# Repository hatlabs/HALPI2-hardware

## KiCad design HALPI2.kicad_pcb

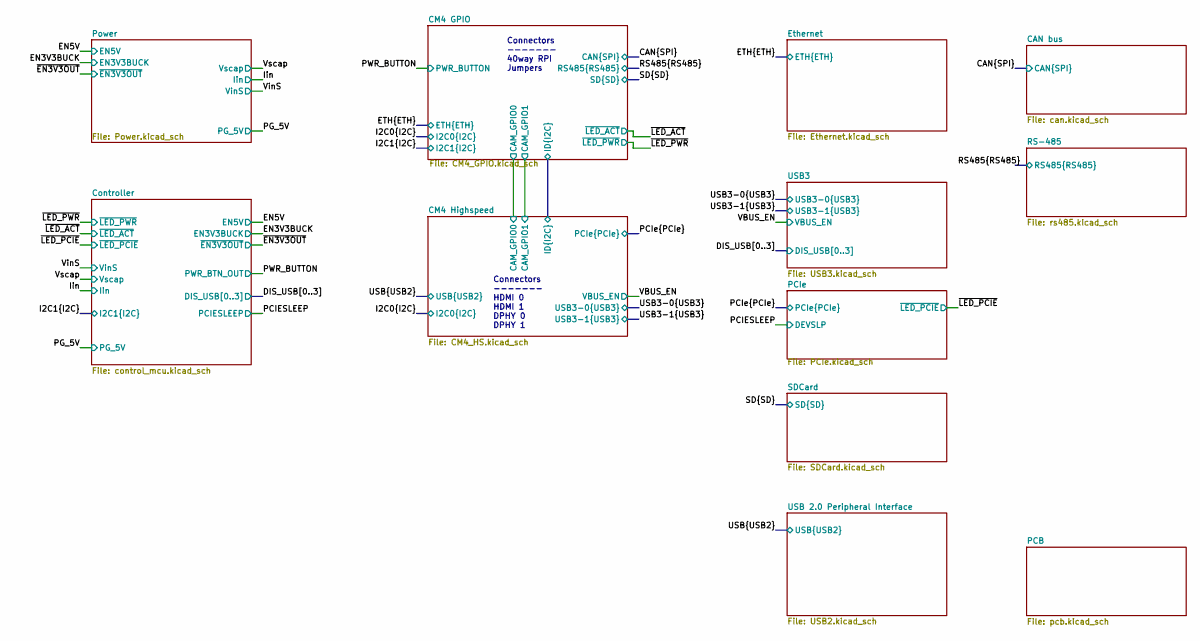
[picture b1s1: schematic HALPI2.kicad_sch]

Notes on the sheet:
Connectors ------- HDMI 0 HDMI 1 DPHY 0 DPHY 1
Connectors ------- 40way RPI Jumpers

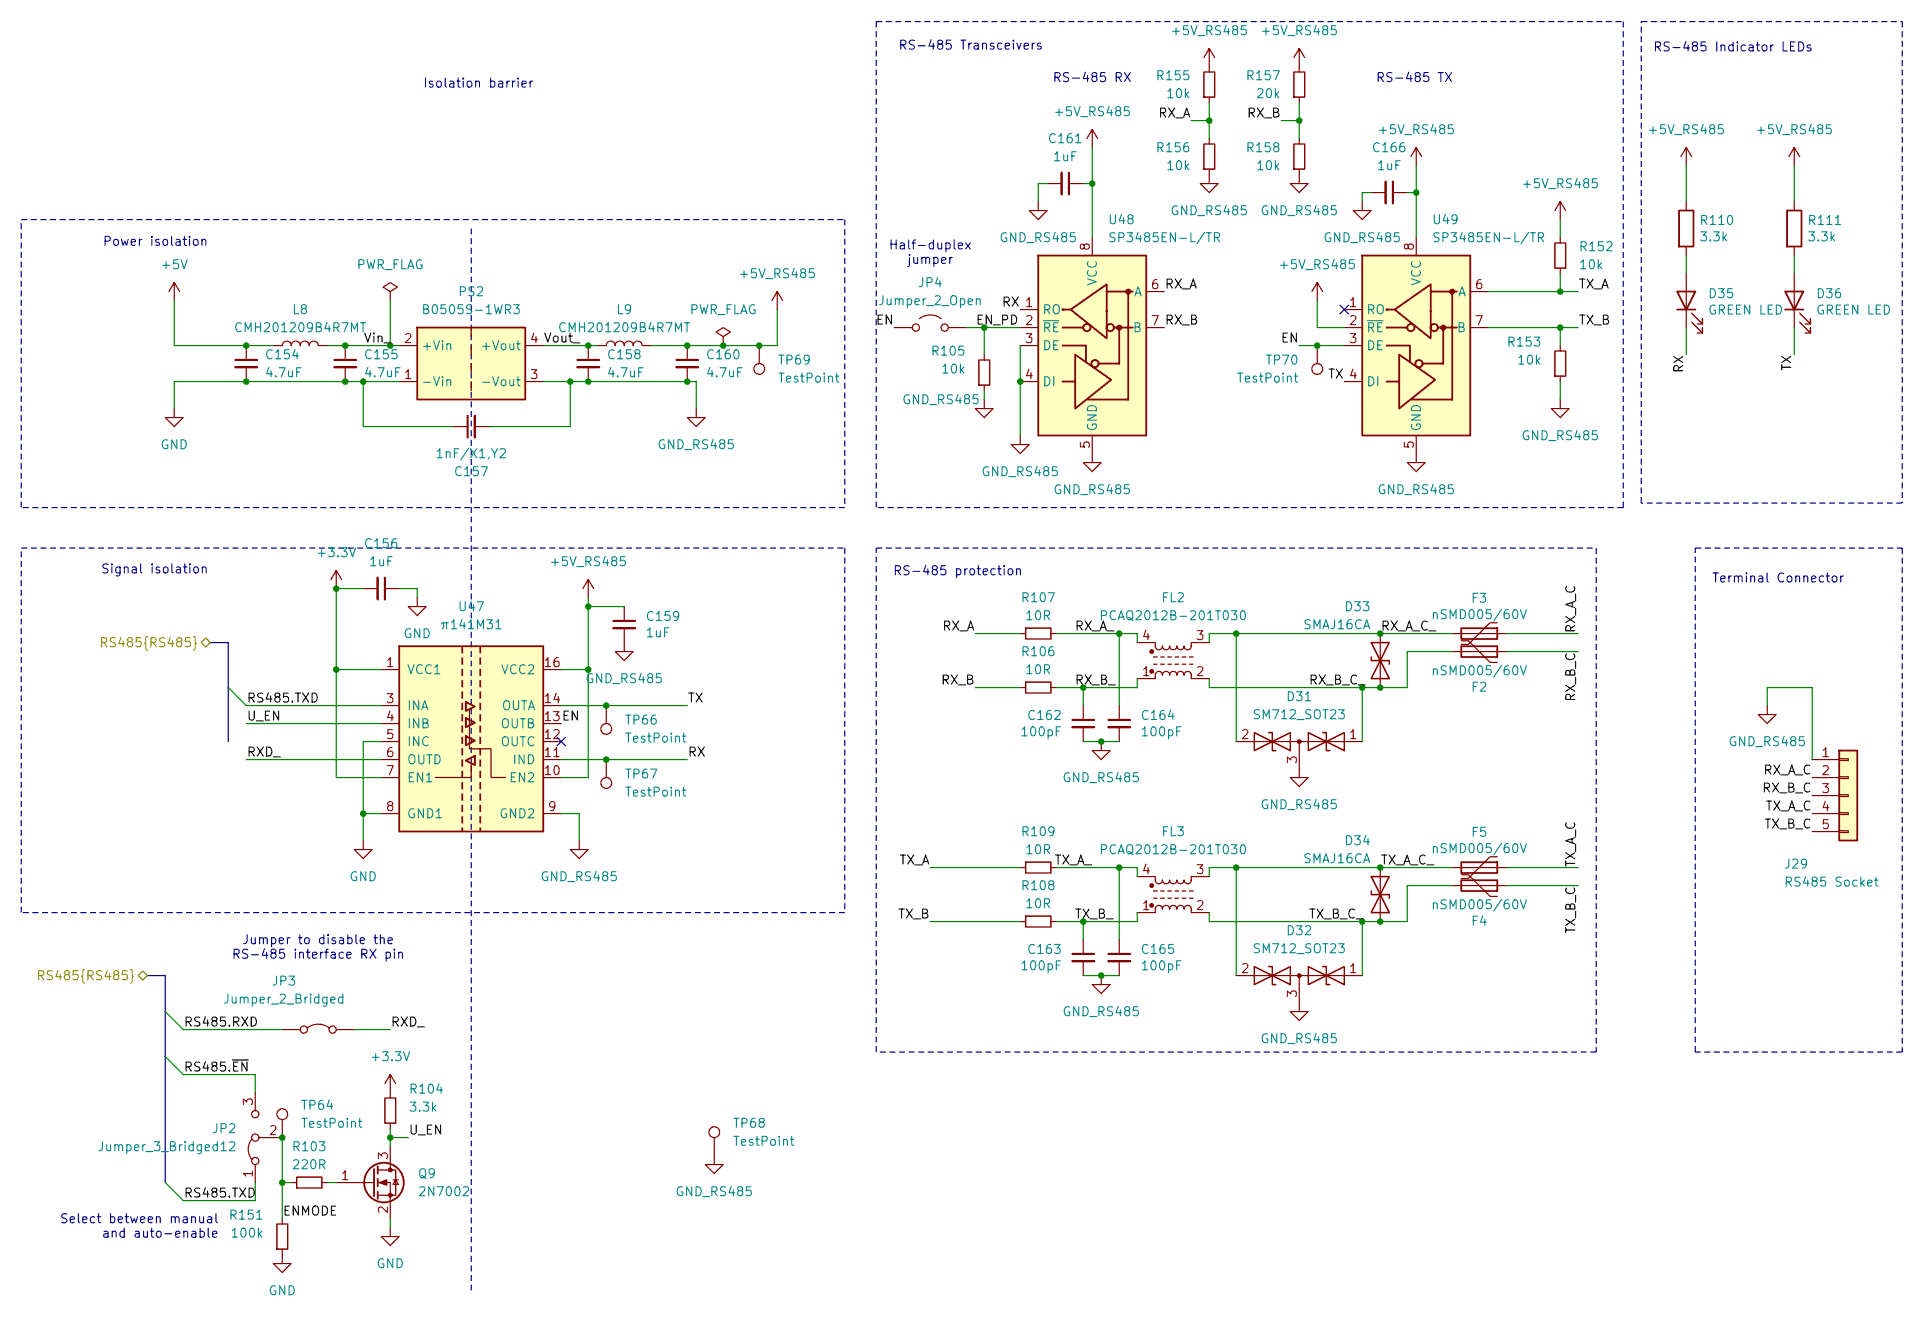
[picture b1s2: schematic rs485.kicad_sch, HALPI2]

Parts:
C154, C155, C158, C160: 4.7uF; C_0603_1608Metric; LCSC C19666
C156, C159, C161, C166: 1uF; C_0402_1005Metric; LCSC C52923
C157: 1nF/X1,Y2; C_1808_4520Metric; LCSC C784081
C162, C163, C164, C165: 100pF; C_0603_1608Metric; LCSC C14858
D31, D32: SM712_SOT23; SOT-23; LCSC C7420375
D33, D34: SMAJ16CA; D_SMA; LCSC C19077537
D35, D36: GREEN LED; LED_0603_1608Metric; LCSC C965804
F2, F3, F4, F5: nSMD005/60V; Fuse_1206_3216Metric; LCSC C2830235
FL2, FL3: PCAQ2012B-201T030; L_CommonModeChoke_PCAQ2012B; LCSC C2926967
J29: RS485 Socket; PhoenixContact_MCV_1,5_5-G-3.81_1x05_P3.81mm_Vertical; LCSC C8391
JP2: Jumper_3_Bridged12; PinHeader_1x03_P2.54mm_Vertical_SMD_Pin1Left; LCSC C41417360
JP3: Jumper_2_Bridged; PinHeader_1x02_P2.54mm_Vertical; LCSC C492401
JP4: Jumper_2_Open; PinHeader_1x02_P2.54mm_Vertical; LCSC C492401
L8, L9: CMH201209B4R7MT; L_0805_2012Metric; LCSC C394959
PS2: B0505S-1WR3; SIP-4_L11.7-W6.0-P2.54_B0305S-1WR3; LCSC C7465178
Q9: 2N7002; SOT-23; LCSC C8545
R103: 220R; R_0402_1005Metric; LCSC C25091
R104, R110, R111: 3.3k; R_0402_1005Metric; LCSC C25890
R105, R152, R153, R155, R156, R158: 10k; R_0402_1005Metric; LCSC C25744
R106, R107, R108, R109: 10R; R_0402_1005Metric; LCSC C25077
R151: 100k; R_0402_1005Metric; LCSC C25741
R157: 20k; R_0402_1005Metric; LCSC C25765
TP64, TP66, TP67, TP69, TP70: TestPoint; TestPoint_Pad_D1.0mm
TP68: TestPoint; TestPoint_Pad_1.5x1.5mm
U47: π141M31; SOIC-16_3.9x9.9mm_P1.27mm; LCSC C471605
U48, U49: SP3485EN-L/TR; SOIC-8_3.9x4.9mm_P1.27mm; LCSC C8963

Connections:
+3.3V: C156.2, R104.2, U47.1 (VCC1), U47.7 (EN1); also elsewhere on the board
+5V: C154.1, L8.1; also elsewhere on the board
+5V_RS485: C159.1, C160.1, C161.1, C166.1, L9.2, R110.1, R111.1, R152.2, R155.2, R157.2, TP69.1 (1_1), U47.10 (EN2), U47.16 (VCC2), U48.8 (VCC), U49.2 (~RE), U49.8 (VCC)
/RS485.RXD: JP3.1 (A); also elsewhere on the board
/RS485.TXD: JP2.1 (A), U47.3 (INA); also elsewhere on the board
/RS485.~EN: JP2.3 (B); also elsewhere on the board
/RS-485/EN: JP4.1 (A), TP70.1 (1_1), U47.13 (OUTB), U49.3 (DE)
/RS-485/ENMODE: JP2.2 (C), R103.1, R151.2, TP64.1 (1_1)
/RS-485/EN_PD: JP4.2 (B), R105.2, U48.2 (~RE)
/RS-485/RX: D35.1 (K), TP67.1 (1_1), U47.11 (IND), U48.1 (RO)
/RS-485/RXD_: JP3.2 (B), U47.6 (OUTD)
/RS-485/RX_A: R107.1, R155.1, R156.2, U48.6 (A)
/RS-485/RX_A_: C164.1, FL2.4, R107.2
/RS-485/RX_A_C: F3.1, J29.2
/RS-485/RX_A_C_: D31.2 (A2), D33.1 (A1), F3.2, FL2.3
/RS-485/RX_B: R106.1, R157.1, R158.2, U48.7 (B)
/RS-485/RX_B_: C162.1, FL2.1, R106.2
/RS-485/RX_B_C: F2.1, J29.3
/RS-485/RX_B_C_: D31.1 (A1), D33.2 (A2), F2.2, FL2.2
/RS-485/TX: D36.1 (K), TP66.1 (1_1), U47.14 (OUTA), U49.4 (DI)
/RS-485/TX_A: R109.1, R152.1, U49.6 (A)
/RS-485/TX_A_: C165.1, FL3.4, R109.2
/RS-485/TX_A_C: F5.1, J29.4
/RS-485/TX_A_C_: D32.2 (A2), D34.1 (A1), F5.2, FL3.3
/RS-485/TX_B: R108.1, R153.2, U49.7 (B)
/RS-485/TX_B_: C163.1, FL3.1, R108.2
/RS-485/TX_B_C: F4.1, J29.5
/RS-485/TX_B_C_: D32.1 (A1), D34.2 (A2), F4.2, FL3.2
/RS-485/U_EN: Q9.3 (D), R104.1, U47.4 (INB)
/RS-485/Vin_: C155.1, L8.2, PS2.2 (+Vin)
/RS-485/Vout_: C158.1, L9.1, PS2.4 (+Vout)
GND: C154.2, C155.2, C156.1, C157.1, PS2.1 (-Vin), Q9.2 (S), R151.1, U47.2 (GND1), U47.5 (INC), U47.8 (GND1); also elsewhere on the board
GND_RS485: C157.2, C158.2, C159.2, C160.2, C161.2, C162.2, C163.2, C164.2, C165.2, C166.2, D31.3 (common), D32.3 (common), J29.1, PS2.3 (-Vout), R105.1, R153.1, R156.1, R158.1, TP68.1 (1_1), U47.9 (GND2), U47.15 (GND2), U48.3 (DE), U48.4 (DI), U48.5 (GND), U49.5 (GND)
unnamed: D35.2 (A), R110.2
unnamed: D36.2 (A), R111.2
unnamed: Q9.1 (G), R103.2

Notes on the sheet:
RS-485 TX
Power isolation
RS-485 RX
Signal isolation
Terminal Connector
Jumper to disable the RS-485 interface RX pin
Isolation barrier
Half-duplex jumper
RS-485 Indicator LEDs
RS-485 Transceivers
Select between manual and auto-enable
RS-485 protection

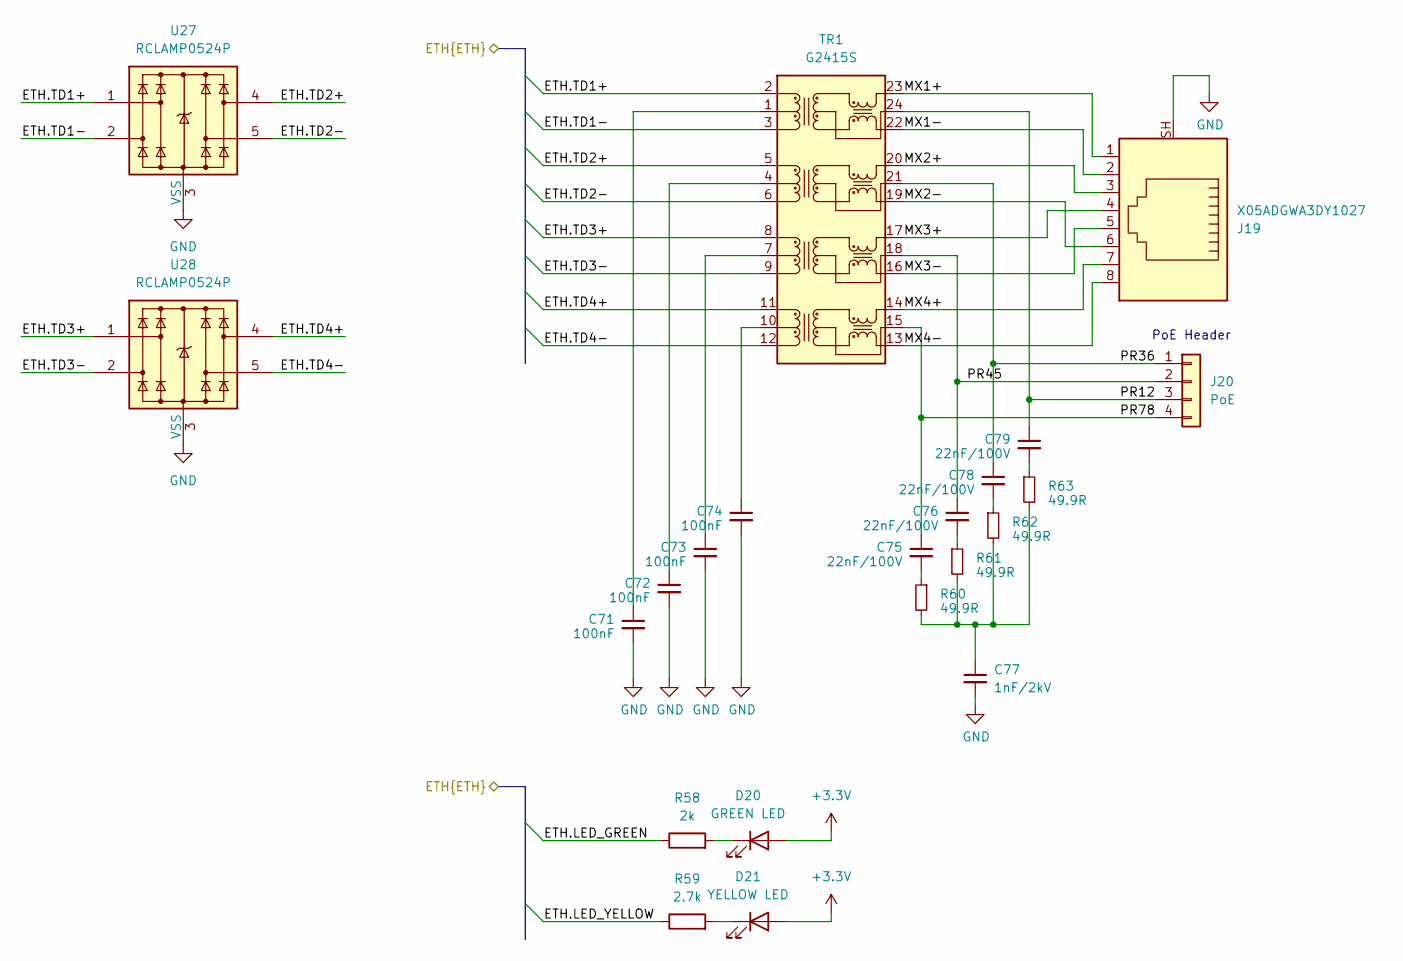
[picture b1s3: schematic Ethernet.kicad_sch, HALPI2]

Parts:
C71, C72, C73, C74: 100nF; C_0402_1005Metric; LCSC C1525
C75, C76, C78, C79: 22nF/100V; C_0603_1608Metric; LCSC C313083
C77: 1nF/2kV; C_1206_3216Metric; LCSC C9196
D20: GREEN LED; LED_0603_1608Metric; LCSC C965804
D21: YELLOW LED; LED_0603_1608Metric; LCSC C89811
J19: X05ADGWA3DY1027; RJ45-TH_XKB_X05ADGWA3DY1027; LCSC C2916454
J20: PoE; PinSocket_2x02_P2.54mm_Vertical_SMD; LCSC C5160817
R58: 2k; R_0603_1608Metric; LCSC C22975
R59: 2.7k; R_0603_1608Metric; LCSC C13167
R60, R61, R62, R63: 49.9R; R_0402_1005Metric; LCSC C25120
TR1: G2415S; Transformer_Ethernet_YDS_30F-51NL_SO-24_7.1x15.1mm; LCSC C3003219
U27, U28: RCLAMP0524P; Diodes_UDFN-10_1.0x2.5mm_P0.5mm; LCSC C907837

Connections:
+3.3V: D20.2 (A), D21.2 (A); also elsewhere on the board
/ETH.LED_GREEN: R58.1; also elsewhere on the board
/ETH.LED_YELLOW: R59.1; also elsewhere on the board
/ETH.TD1+: TR1.2 (TD1+), U27.1, U27.10; also elsewhere on the board
/ETH.TD1-: TR1.3 (TD1-), U27.2, U27.9; also elsewhere on the board
/ETH.TD2+: TR1.5 (TD2+), U27.4, U27.7; also elsewhere on the board
/ETH.TD2-: TR1.6 (TD2-), U27.5, U27.6; also elsewhere on the board
/ETH.TD3+: TR1.8 (TD3+), U28.1, U28.10; also elsewhere on the board
/ETH.TD3-: TR1.9 (TD3-), U28.2, U28.9; also elsewhere on the board
/ETH.TD4+: TR1.11 (TD4+), U28.4, U28.7; also elsewhere on the board
/ETH.TD4-: TR1.12 (TD4-), U28.5, U28.6; also elsewhere on the board
/Ethernet/MX1+: J19.1, TR1.23 (MX1+)
/Ethernet/MX1-: J19.2, TR1.22 (MX1-)
/Ethernet/MX2+: J19.3, TR1.20 (MX2+)
/Ethernet/MX2-: J19.6, TR1.19 (MX2-)
/Ethernet/MX3+: J19.4, TR1.17 (MX3+)
/Ethernet/MX3-: J19.5, TR1.16 (MX3-)
/Ethernet/MX4+: J19.7, TR1.14 (MX4+)
/Ethernet/MX4-: J19.8, TR1.13 (MX4-)
/Ethernet/PR12: C79.1, J20.3, TR1.24 (CT)
/Ethernet/PR36: C78.1, J20.1, TR1.21 (CT)
/Ethernet/PR45: C76.1, J20.2, TR1.18 (CT)
/Ethernet/PR78: C75.1, J20.4, TR1.15 (CT)
GND: C71.2, C72.2, C73.2, C74.2, C77.2, J19.SH, U27.3 (VSS), U27.8 (VSS), U28.3 (VSS), U28.8 (VSS); also elsewhere on the board
unnamed: C71.1, TR1.1 (CT)
unnamed: C72.1, TR1.4 (CT)
unnamed: C73.1, TR1.7 (CT)
unnamed: C74.1, TR1.10 (CT)
unnamed: C75.2, R60.1
unnamed: C76.2, R61.1
unnamed: C77.1, R60.2, R61.2, R62.2, R63.2
unnamed: C78.2, R62.1
unnamed: C79.2, R63.1
unnamed: D20.1 (K), R58.2
unnamed: D21.1 (K), R59.2

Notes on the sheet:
PoE Header

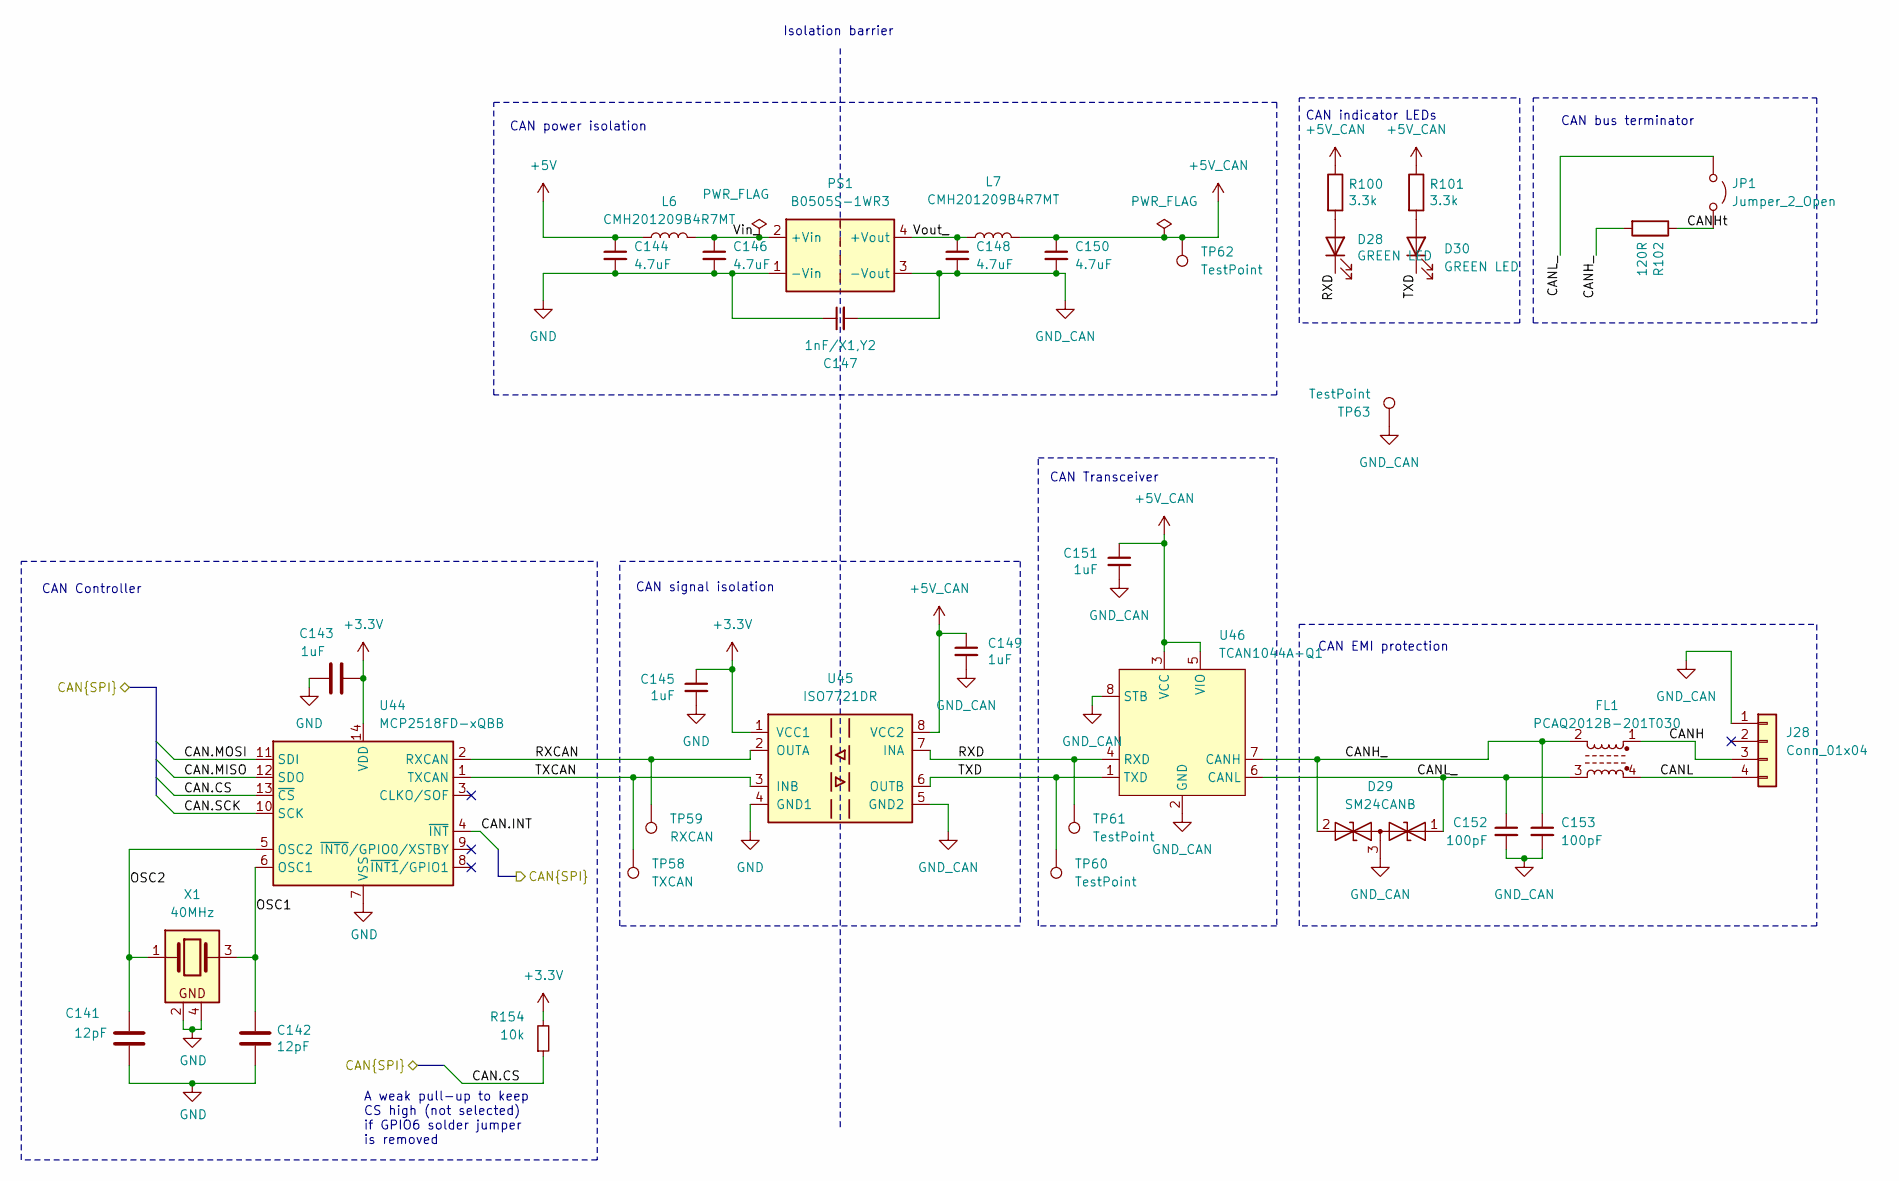
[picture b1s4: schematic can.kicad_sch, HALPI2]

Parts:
C141, C142: 12pF; C_0402_1005Metric; LCSC C1547
C143, C145, C149, C151: 1uF; C_0402_1005Metric; LCSC C52923
C144, C146, C148, C150: 4.7uF; C_0603_1608Metric; LCSC C19666
C147: 1nF/X1,Y2; C_1808_4520Metric; LCSC C784081
C152, C153: 100pF; C_0603_1608Metric; LCSC C14858
D28, D30: GREEN LED; LED_0603_1608Metric; LCSC C965804
D29: SM24CANB; SOT-23; LCSC C19185908
FL1: PCAQ2012B-201T030; L_CommonModeChoke_PCAQ2012B; LCSC C2926967
J28: Conn_01x04; PhoenixContact_MCV_1,5_4-G-3.81_1x04_P3.81mm_Vertical; LCSC C8410
JP1: Jumper_2_Open; PinHeader_1x02_P2.54mm_Vertical; LCSC C492401
L6, L7: CMH201209B4R7MT; L_0805_2012Metric; LCSC C394959
PS1: B0505S-1WR3; SIP-4_L11.7-W6.0-P2.54_B0305S-1WR3; LCSC C7465178
R100, R101: 3.3k; R_0402_1005Metric; LCSC C25890
R102: 120R; R_0805_2012Metric; LCSC C17437
R154: 10k; R_0402_1005Metric; LCSC C25744
TP58: TXCAN; TestPoint_Pad_D1.0mm
TP59: RXCAN; TestPoint_Pad_D1.0mm
TP60, TP61, TP62: TestPoint; TestPoint_Pad_D1.0mm
TP63: TestPoint; TestPoint_Pad_1.5x1.5mm
U44: MCP2518FD-xQBB; DFN-14-1EP_3x4.5mm_P0.65mm_EP1.65x4.25mm; LCSC C621395
U45: ISO7721DR; SOIC-8_3.9x4.9mm_P1.27mm; LCSC C366164
U46: TCAN1044A-Q1; SOIC-8_3.9x4.9mm_P1.27mm; LCSC C3235016
X1: 40MHz; Crystal_SMD_3225-4Pin_3.2x2.5mm; LCSC C5380554

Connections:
+3.3V: C143.2, C145.1, R154.2, U44.14 (VDD), U45.1 (VCC1); also elsewhere on the board
+5V: C144.1, L6.1; also elsewhere on the board
+5V_CAN: C149.1, C150.1, C151.1, L7.2, R100.1, R101.1, TP62.1 (1_1), U45.8 (VCC2), U46.3 (VCC), U46.5 (VIO)
/CAN bus/CANH: FL1.1, J28.3
/CAN bus/CANH_: C153.1, D29.2 (A2), FL1.2, R102.2, U46.7 (CANH)
/CAN bus/CANHt: JP1.2 (B), R102.1
/CAN bus/CANL: FL1.4, J28.4
/CAN bus/CANL_: C152.1, D29.1 (A1), FL1.3, JP1.1 (A), U46.6 (CANL)
/CAN bus/OSC1: C142.1, U44.6 (OSC1), X1.3
/CAN bus/OSC2: C141.1, U44.5 (OSC2), X1.1
/CAN bus/RXCAN: TP59.1 (1_1), U44.2 (RXCAN), U45.2 (OUTA)
/CAN bus/RXD: D28.1 (K), TP61.1 (1_1), U45.7 (INA), U46.4 (RXD)
/CAN bus/TXCAN: TP58.1 (1_1), U44.1 (TXCAN), U45.3 (INB)
/CAN bus/TXD: D30.1 (K), TP60.1 (1_1), U45.6 (OUTB), U46.1 (TXD)
/CAN bus/Vin_: C146.1, L6.2, PS1.2 (+Vin)
/CAN bus/Vout_: C148.1, L7.1, PS1.4 (+Vout)
/CAN.CS: R154.1, U44.13 (~CS); also elsewhere on the board
/CAN.INT: U44.4 (~INT); also elsewhere on the board
/CAN.MISO: U44.12 (SDO); also elsewhere on the board
/CAN.MOSI: U44.11 (SDI); also elsewhere on the board
/CAN.SCK: U44.10 (SCK); also elsewhere on the board
GND: C141.2, C142.2, C143.1, C144.2, C145.2, C146.2, C147.1, PS1.1 (-Vin), U44.7 (VSS), U44.15 (VSS), U45.4 (GND1), X1.2, X1.4; also elsewhere on the board
GND_CAN: C147.2, C148.2, C149.2, C150.2, C151.2, C152.2, C153.2, D29.3 (common), J28.1, PS1.3 (-Vout), TP63.1 (1_1), U45.5 (GND2), U46.2 (GND), U46.8 (STB)
unnamed: D28.2 (A), R100.2
unnamed: D30.2 (A), R101.2

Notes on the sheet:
CAN signal isolation
CAN Transceiver
CAN Controller
Isolation barrier
CAN power isolation
CAN bus terminator
CAN EMI protection
CAN indicator LEDs
A weak pull-up to keep CS high (not selected) if GPIO6 solder jumper is removed

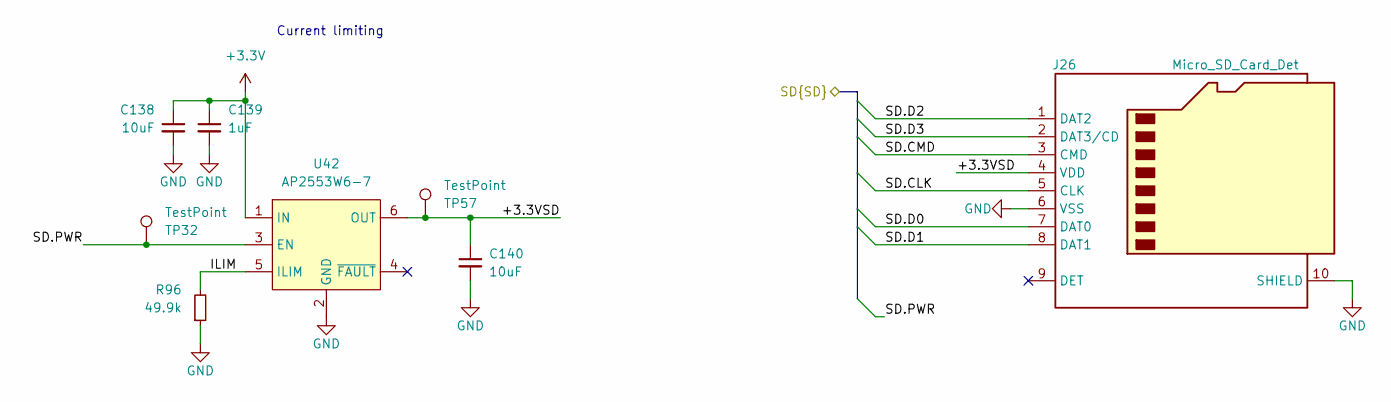
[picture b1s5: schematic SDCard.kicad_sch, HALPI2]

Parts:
C138, C140: 10uF; C_0805_2012Metric; LCSC C15850
C139: 1uF; C_0402_1005Metric; LCSC C52923
J26: Micro_SD_Card_Det; MicroSD_SHOU-HAN_TF-PUSH; LCSC C393941
R96: 49.9k; R_0603_1608Metric; LCSC C23184
TP32, TP57: TestPoint; TestPoint_Pad_D1.0mm
U42: AP2553W6-7; SOT-23-6; LCSC C212302

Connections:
+3.3V: C138.1, C139.1, U42.1 (IN); also elsewhere on the board
/SD.CLK: J26.5 (CLK); also elsewhere on the board
/SD.CMD: J26.3 (CMD); also elsewhere on the board
/SD.D0: J26.7 (DAT0); also elsewhere on the board
/SD.D1: J26.8 (DAT1); also elsewhere on the board
/SD.D2: J26.1 (DAT2); also elsewhere on the board
/SD.D3: J26.2 (DAT3/CD); also elsewhere on the board
/SD.PWR: TP32.1 (1_1), U42.3 (EN); also elsewhere on the board
/SDCard/+3.3VSD: C140.1, J26.4 (VDD), TP57.1 (1_1), U42.6 (OUT)
/SDCard/ILIM: R96.2, U42.5 (ILIM)
GND: C138.2, C139.2, C140.2, J26.6 (VSS), J26.10 (SHIELD), R96.1, U42.2 (GND); also elsewhere on the board

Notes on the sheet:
Current limiting

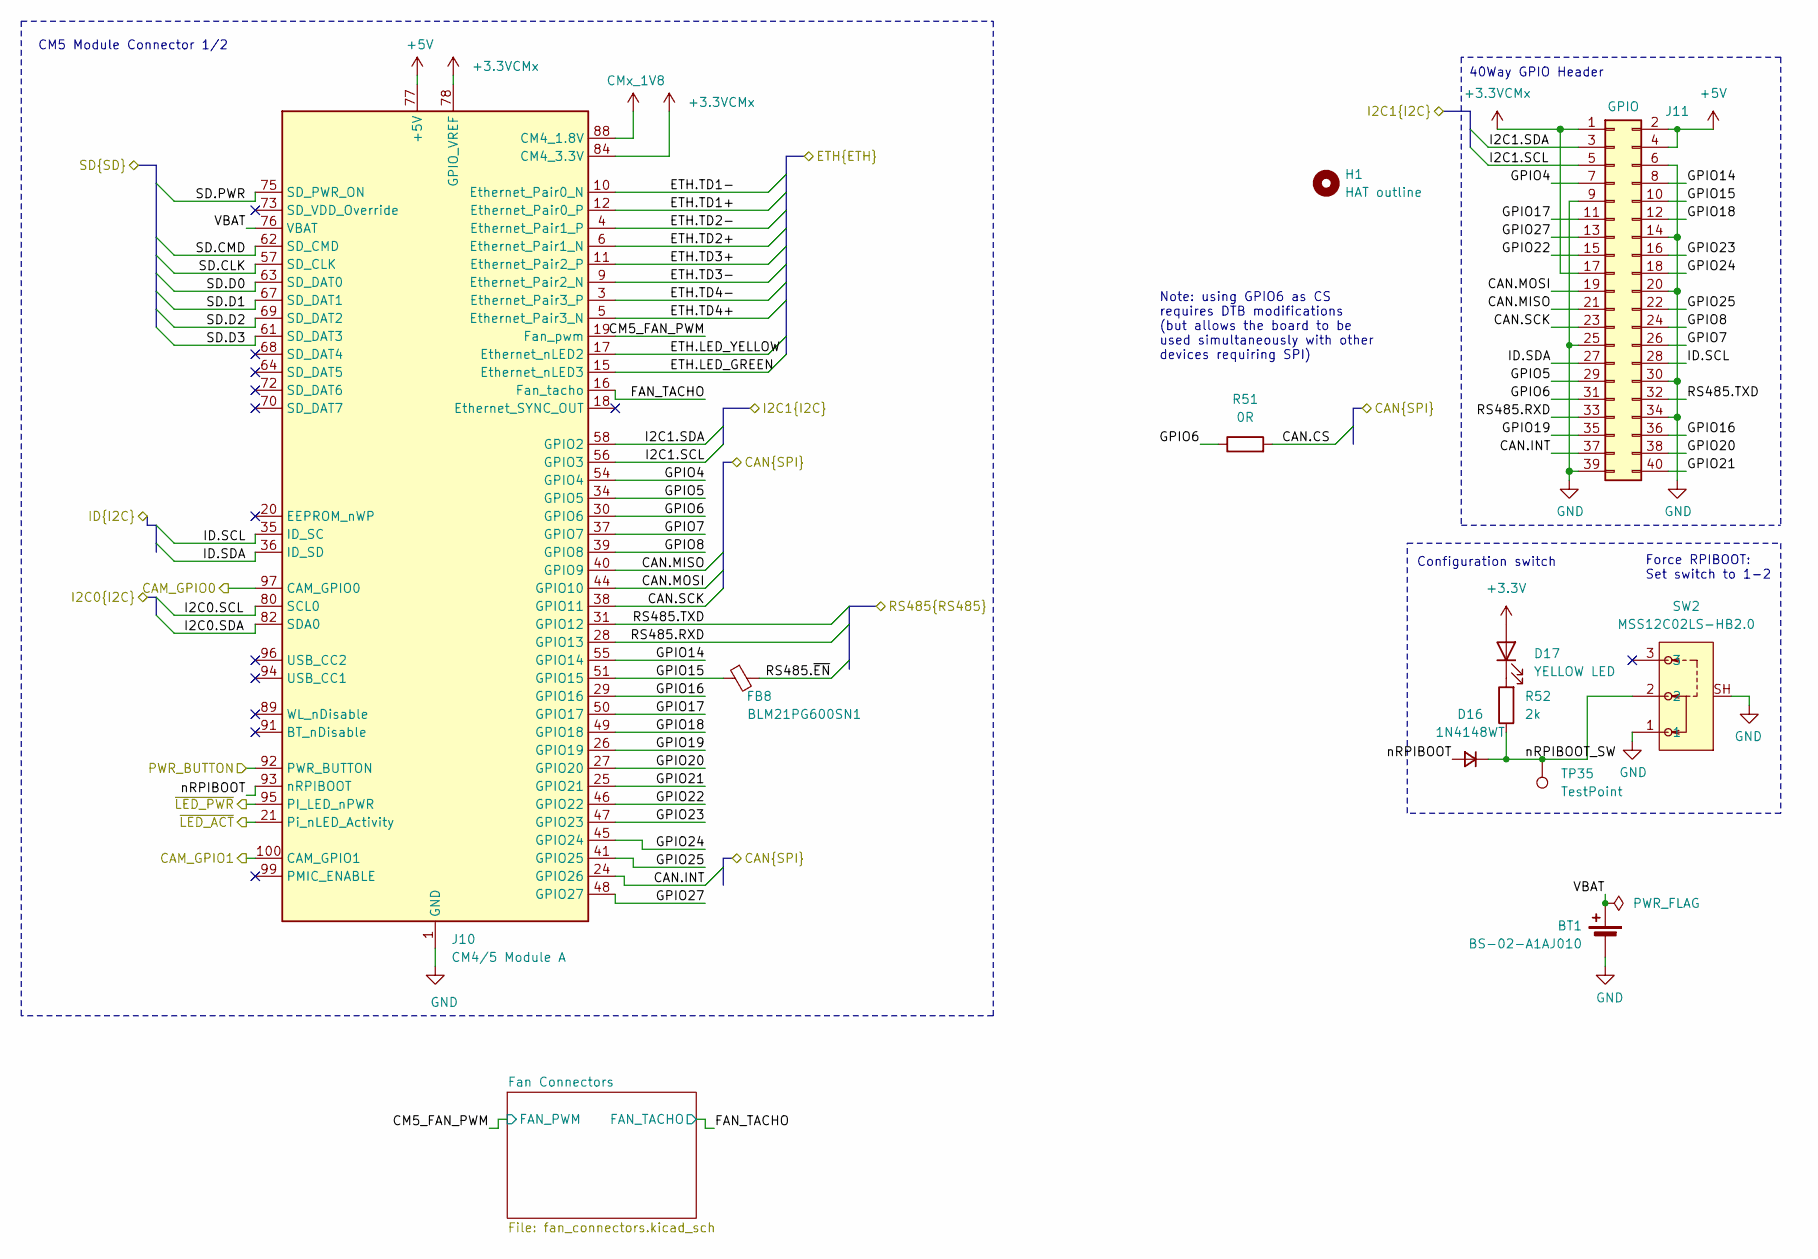
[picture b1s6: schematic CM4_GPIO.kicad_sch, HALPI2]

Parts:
BT1: BS-02-A1AJ010; BatteryHolder-TH_BS-02-A1AJ010; LCSC C5239862
D16: 1N4148WT; D_SOD-523; LCSC C7420320
D17: YELLOW LED; LED_0603_1608Metric; LCSC C89811
FB8: BLM21PG600SN1; L_0805_2012Metric; LCSC C18305
H1: HAT outline; RPi_HAT_Outline
J10: CM4/5 Module A; Hirose_DF40_DF40C-100DS-0.4V_2x50_P0.40mm_Vertical; LCSC C424649
J11: GPIO; PinHeader_2x20_P2.54mm_Vertical; LCSC C429965
R51: 0R; R_0603_1608Metric_Pad0.98x0.95mm_HandSolder; LCSC C21189
R52: 2k; R_0402_1005Metric; LCSC C4109
SW2: MSS12C02LS-HB2.0; SW-SMD_MSS12C02LS-HB2.0-1; LCSC C3008584
TP35: TestPoint; TestPoint_Pad_D1.0mm

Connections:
+3.3V: D17.2 (A); also elsewhere on the board
+3.3VCMx: J10.78 (GPIO_VREF), J10.84 (CM4_3.3V), J10.86 (CM4_3.3V), J11.1, J11.17; also elsewhere on the board
+5V: J10.77 (+5V), J10.79 (+5V), J10.81 (+5V), J10.83 (+5V), J10.85 (+5V), J10.87 (+5V), J11.2, J11.4; also elsewhere on the board
/CAN.CS: R51.2; also elsewhere on the board
/CAN.INT: J10.24 (GPIO26), J11.37; also elsewhere on the board
/CAN.MISO: J10.40 (GPIO9), J11.21; also elsewhere on the board
/CAN.MOSI: J10.44 (GPIO10), J11.19; also elsewhere on the board
/CAN.SCK: J10.38 (GPIO11), J11.23; also elsewhere on the board
/CM4 GPIO/CAM_GPIO0: J10.97 (CAM_GPIO0); also elsewhere on the board
/CM4 GPIO/CAM_GPIO1: J10.100 (CAM_GPIO1); also elsewhere on the board
/CM4 GPIO/CM5_FAN_PWM: J10.19 (Fan_pwm); also elsewhere on the board
/CM4 GPIO/FAN_TACHO: J10.16 (Fan_tacho); also elsewhere on the board
/CM4 GPIO/GPIO4: J10.54 (GPIO4), J11.7
/CM4 GPIO/GPIO5: J10.34 (GPIO5), J11.29
/CM4 GPIO/GPIO6: J10.30 (GPIO6), J11.31, R51.1
/CM4 GPIO/GPIO7: J10.37 (GPIO7), J11.26
/CM4 GPIO/GPIO8: J10.39 (GPIO8), J11.24
/CM4 GPIO/GPIO14: J10.55 (GPIO14), J11.8
/CM4 GPIO/GPIO15: FB8.1, J10.51 (GPIO15), J11.10
/CM4 GPIO/GPIO16: J10.29 (GPIO16), J11.36
/CM4 GPIO/GPIO17: J10.50 (GPIO17), J11.11
/CM4 GPIO/GPIO18: J10.49 (GPIO18), J11.12
/CM4 GPIO/GPIO19: J10.26 (GPIO19), J11.35
/CM4 GPIO/GPIO20: J10.27 (GPIO20), J11.38
/CM4 GPIO/GPIO21: J10.25 (GPIO21), J11.40
/CM4 GPIO/GPIO22: J10.46 (GPIO22), J11.15
/CM4 GPIO/GPIO23: J10.47 (GPIO23), J11.16
/CM4 GPIO/GPIO24: J10.45 (GPIO24), J11.18
/CM4 GPIO/GPIO25: J10.41 (GPIO25), J11.22
/CM4 GPIO/GPIO27: J10.48 (GPIO27), J11.13
/CM4 GPIO/ID.SCL: J10.35 (ID_SC), J11.28; also elsewhere on the board
/CM4 GPIO/ID.SDA: J10.36 (ID_SD), J11.27; also elsewhere on the board
/CM4 GPIO/VBAT: BT1.1 (+), J10.76 (VBAT)
/CM4 GPIO/nRPIBOOT: D16.2 (A), J10.93 (nRPIBOOT)
/CM4 GPIO/nRPIBOOT_SW: D16.1 (K), R52.1, SW2.2, TP35.1 (1_1)
/ETH.LED_GREEN: J10.15 (Ethernet_nLED3); also elsewhere on the board
/ETH.LED_YELLOW: J10.17 (Ethernet_nLED2); also elsewhere on the board
/ETH.TD1+: J10.12 (Ethernet_Pair0_P); also elsewhere on the board
/ETH.TD1-: J10.10 (Ethernet_Pair0_N); also elsewhere on the board
/ETH.TD2+: J10.6 (Ethernet_Pair1_N); also elsewhere on the board
/ETH.TD2-: J10.4 (Ethernet_Pair1_P); also elsewhere on the board
/ETH.TD3+: J10.11 (Ethernet_Pair2_P); also elsewhere on the board
/ETH.TD3-: J10.9 (Ethernet_Pair2_N); also elsewhere on the board
/ETH.TD4+: J10.5 (Ethernet_Pair3_N); also elsewhere on the board
/ETH.TD4-: J10.3 (Ethernet_Pair3_P); also elsewhere on the board
/I2C0.SCL: J10.80 (SCL0); also elsewhere on the board
/I2C0.SDA: J10.82 (SDA0); also elsewhere on the board
/I2C1.SCL: J10.56 (GPIO3), J11.5; also elsewhere on the board
/I2C1.SDA: J10.58 (GPIO2), J11.3; also elsewhere on the board
/PWR_BUTTON: J10.92 (PWR_BUTTON); also elsewhere on the board
/RS485.RXD: J10.28 (GPIO13), J11.33; also elsewhere on the board
/RS485.TXD: J10.31 (GPIO12), J11.32; also elsewhere on the board
/RS485.~EN: FB8.2; also elsewhere on the board
/SD.CLK: J10.57 (SD_CLK); also elsewhere on the board
/SD.CMD: J10.62 (SD_CMD); also elsewhere on the board
/SD.D0: J10.63 (SD_DAT0); also elsewhere on the board
/SD.D1: J10.67 (SD_DAT1); also elsewhere on the board
/SD.D2: J10.69 (SD_DAT2); also elsewhere on the board
/SD.D3: J10.61 (SD_DAT3); also elsewhere on the board
/SD.PWR: J10.75 (SD_PWR_ON); also elsewhere on the board
/~LED_ACT: J10.21 (Pi_nLED_Activity); also elsewhere on the board
/~LED_PWR: J10.95 (PI_LED_nPWR); also elsewhere on the board
CMx_1V8: J10.88 (CM4_1.8V), J10.90 (CM4_1.8V)
GND: BT1.2 (-), J10.1 (GND), J10.2 (GND), J10.7 (GND), J10.8 (GND), J10.13 (GND), J10.14 (GND), J10.22 (GND), J10.23 (GND), J10.32 (GND), J10.33 (GND), J10.42 (GND), J10.43 (GND), J10.52 (GND), J10.53 (GND), J10.59 (GND), J10.60 (GND), J10.65 (GND), J10.66 (GND), J10.71 (GND), J10.74 (GND), J10.98 (GND), J11.6, J11.9, J11.14, J11.20, J11.25, J11.30, J11.34, J11.39, SW2.1, SW2.SH; also elsewhere on the board
unnamed: D17.1 (K), R52.2

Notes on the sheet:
40Way GPIO Header
Note: using GPIO6 as CS requires DTB modifications (but allows the board to be used simultaneously with other devices requiring SPI)
Configuration switch
Force RPIBOOT: Set switch to 1-2
CM5 Module Connector 1/2

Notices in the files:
CM4_GPIO.kicad_sch:
HALPI2 is licensed under CERN-OHL-S v2.
